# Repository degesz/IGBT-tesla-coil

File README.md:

# IGBT-tesla-coil
tesla coil design with IGBT swithced H bridge

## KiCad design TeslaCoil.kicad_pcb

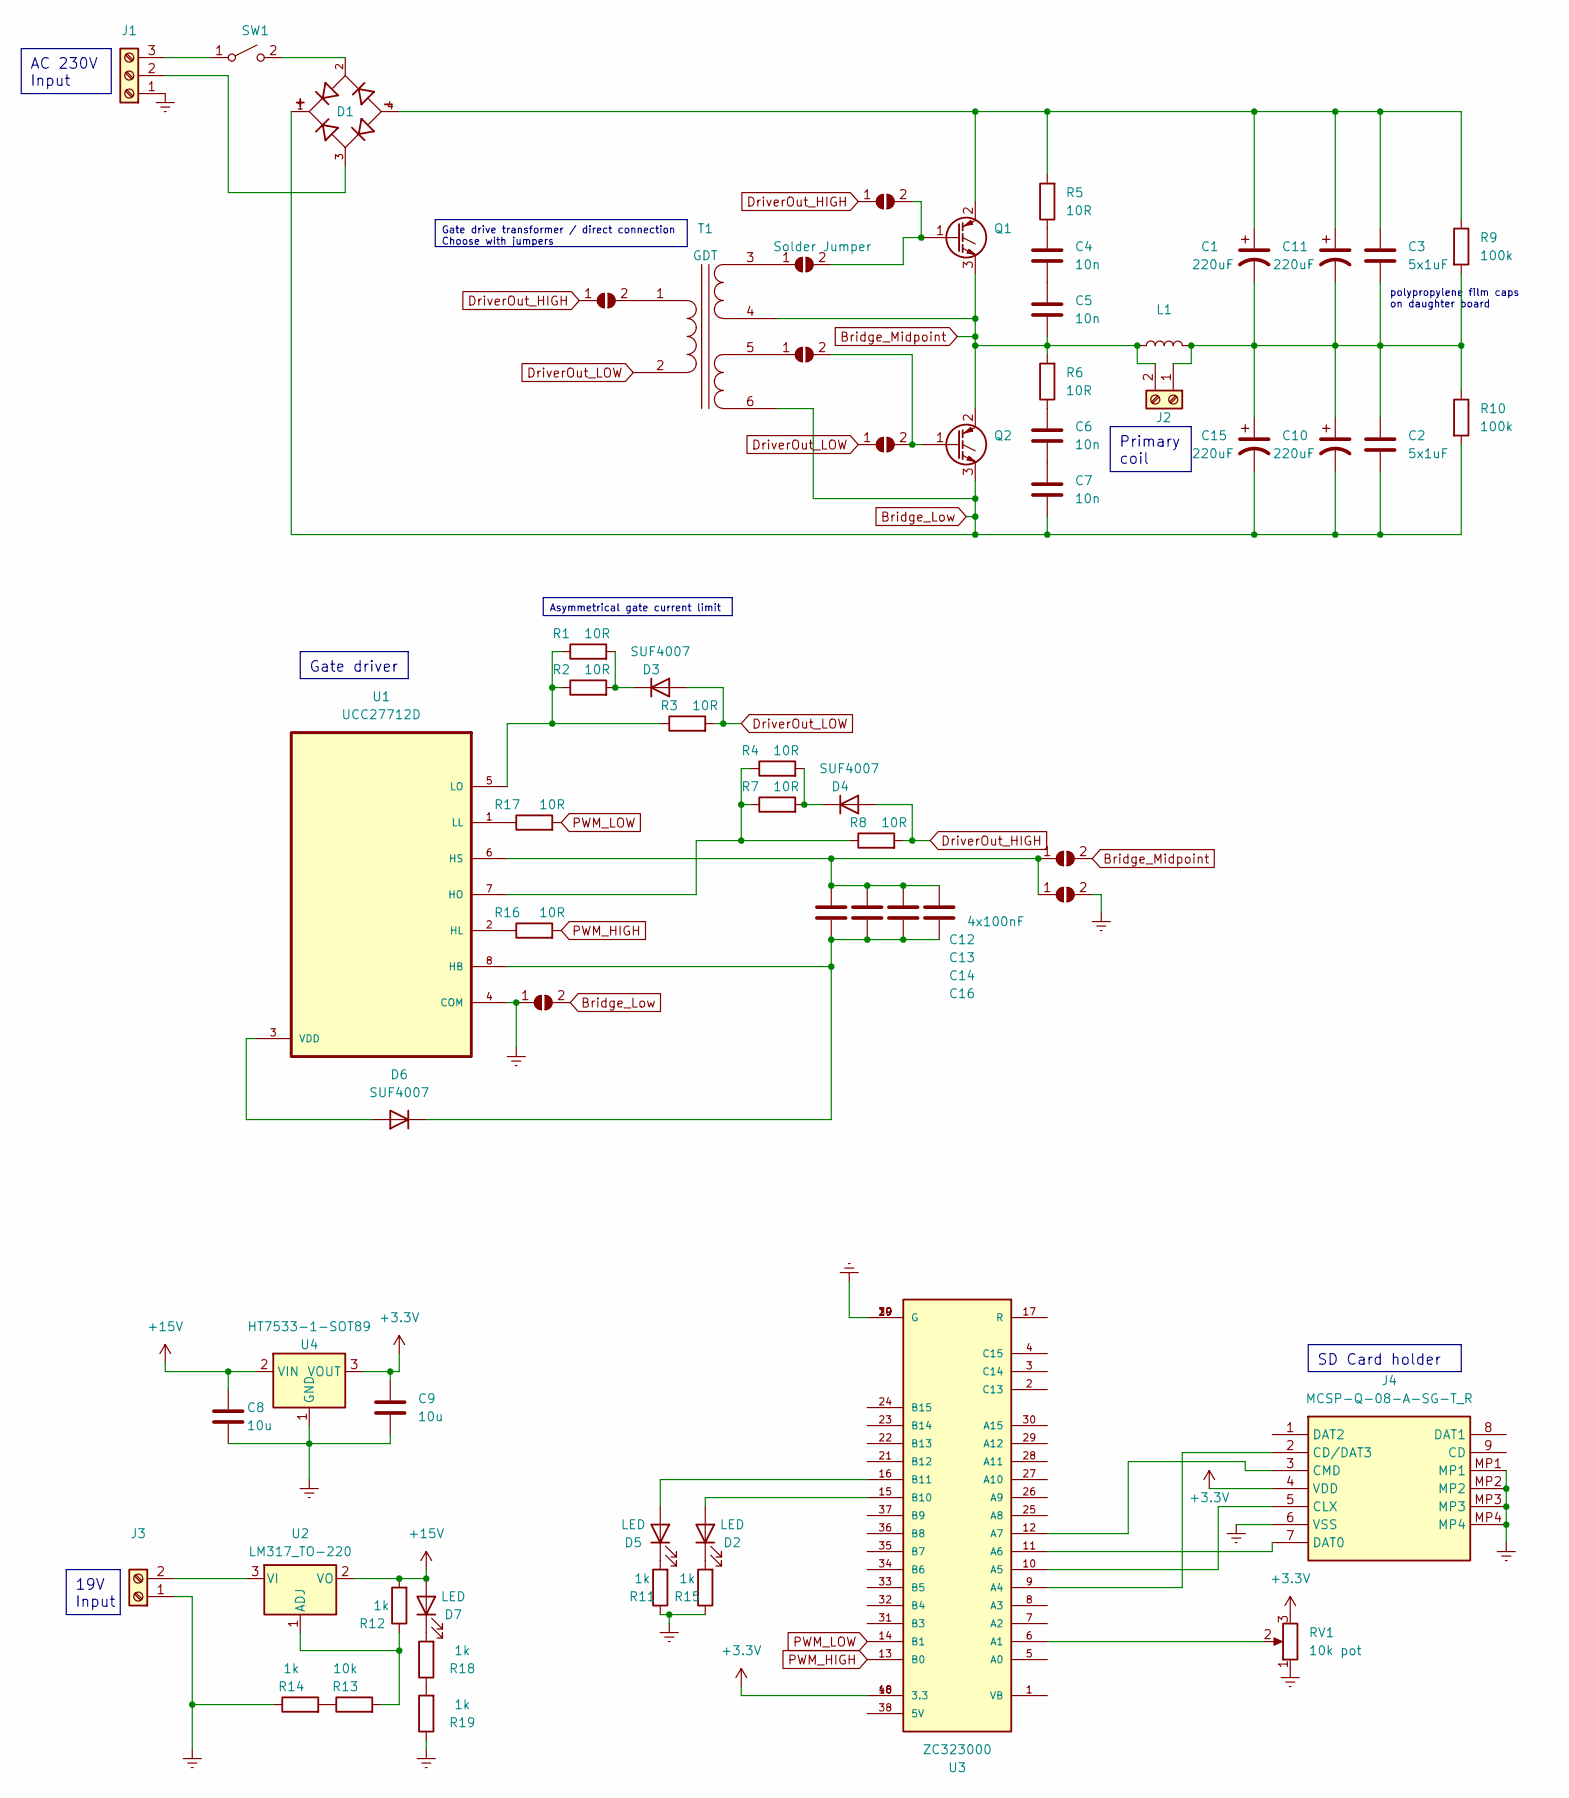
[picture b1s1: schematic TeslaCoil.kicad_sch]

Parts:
C1, C10, C11, C15: 220uF; CP_Radial_D22.0mm_P10.00mm_SnapIn
C2, C3: 5x1uF; C_Rect_L18.0mm_W5.0mm_P15.00mm_FKS3_FKP3
C4, C5, C6, C7: 10n; C_Rect_L13.0mm_W5.0mm_P10.00mm_FKS3_FKP3_MKS4
C8, C9: 10u; C_0805_2012Metric_Pad1.18x1.45mm_HandSolder
C12, C13, C14: 100nF; C_0603_1608Metric
C16: 4x100nF; C_0603_1608Metric
D1: GBJ1008-BP; GBJ1008-BP_DIOB_GBJ1008-BP
D2, D5, D7: LED; LED_0805_2012Metric
D3, D4, D6: SUF4007; D_MELF_Handsoldering
J1: Screw_Terminal_01x03; TerminalBlock_4Ucon_1x03_P3.50mm_Horizontal
J2, J3: Screw_Terminal_01x02; TerminalBlock_4Ucon_1x02_P3.50mm_Horizontal
J4: MCSP-Q-08-A-SG-T_R; MCSPQ08ASGTR; Manufacturer_Part_Number MCSP-Q-08-A-SG-T/R
JP1, JP2, JP3, JP4, JP5, JP6, JP7, JP8: Solder Jumper; SolderJumper-2_P1.3mm_Open_TrianglePad1.0x1.5mm
L1: L
Q1, Q2: Q_NIGBT_GCE; TO-247-3_Vertical
R1, R2, R3, R4, R7, R8, R16, R17: 10R; R_0603_1608Metric_Pad0.98x0.95mm_HandSolder
R5, R6: 10R; R_Axial_Power_L25.0mm_W9.0mm_P10.16mm_Vertical
R9, R10: 100k; R_Axial_DIN0207_L6.3mm_D2.5mm_P7.62mm_Horizontal
R11, R12, R14, R15, R18, R19: 1k; R_0603_1608Metric_Pad0.98x0.95mm_HandSolder
R13: 10k; R_0603_1608Metric_Pad0.98x0.95mm_HandSolder
RV1: 10k pot; potentiometer
SW1: SW_SPST; Rocker switch
T1: GDT; Transformer_Toroid_Tapped_Horizontal_D10.5mm_Amidon-T37
U1: UCC27712D; UCC27712D_SOIC127P599X175-8N
U2: LM317_TO-220; TO-220-3_Vertical
U3: ZC323000; ZC323000_MODULE_ZC323000; PARTREV N/A
U4: HT7533-1-SOT89; SOT-89-3

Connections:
+3.3V: C9.1, J4.4 (VDD), RV1.3, U3.18 (3.3), U3.40 (3.3), U4.3 (VOUT)
+15V: C8.1, D7.2 (A), R12.2, U2.2 (VO), U4.2 (VIN)
Bridge_Low: C2.2, C7.2, C10.2, C15.2, D1.1, JP8.2 (B), Q2.3 (E), R10.2, T1.6 (SD)
Bridge_Midpoint: C5.2, J2.2, JP6.2 (B), L1.1, Q1.3 (E), Q2.2 (C), R6.2, T1.4 (SB)
DriverOut_HIGH: D4.2 (A), JP3.1 (A), JP5.1 (A), R8.2
DriverOut_LOW: D3.2 (A), JP4.1 (A), R3.2, T1.2 (AB)
Earth: C8.2, C9.2, J1.1, J3.1, J4.6 (VSS), J4.MP1, J4.MP2, J4.MP3, J4.MP4, JP7.2 (B), JP8.1 (A), R11.1, R14.1, R15.1, R19.1, RV1.1, U1.4 (COM), U3.19 (G), U3.20 (G), U3.39 (G), U4.1 (GND)
unnamed: C4.1, R5.1
unnamed: C4.2, C5.1
unnamed: C6.1, R6.1
unnamed: C6.2, C7.1
unnamed: D2.2 (A), U3.15 (B10)
unnamed: D2.1 (K), R15.2
unnamed: D3.1 (K), R1.2, R2.2
unnamed: D4.1 (K), R4.2, R7.2
unnamed: D5.2 (A), U3.16 (B11)
unnamed: D5.1 (K), R11.2
unnamed: D6.2 (A), U1.3 (VDD)
unnamed: C12.2, C13.2, C14.2, C16.2, D6.1 (K), U1.8 (HB)
unnamed: D7.1 (K), R18.2
unnamed: D1.3, J1.2
unnamed: J1.3, SW1.1 (A)
unnamed: C1.2, C2.1, C3.2, C10.1, C11.2, C15.1, J2.1, L1.2, R9.2, R10.1
unnamed: J3.2, U2.3 (VI)
unnamed: J4.2 (CD/DAT3), U3.9 (A4)
unnamed: J4.5 (CLX), U3.10 (A5)
unnamed: J4.3 (CMD), U3.12 (A7)
unnamed: J4.7 (DAT0), U3.11 (A6)
unnamed: JP1.1 (A), T1.3 (SA)
unnamed: JP1.2 (B), JP5.2 (B), Q1.1 (G)
unnamed: JP2.1 (A), T1.5 (SC)
unnamed: JP2.2 (B), JP4.2 (B), Q2.1 (G)
unnamed: JP3.2 (B), T1.1 (AA)
unnamed: C12.1, C13.1, C14.1, C16.1, JP6.1 (A), JP7.1 (A), U1.6 (HS)
unnamed: C1.1, C3.1, C11.1, D1.4, Q1.2 (C), R5.2, R9.1
unnamed: R13.1, R14.2
unnamed: R18.1, R19.2
unnamed: D1.2, SW1.2 (B)
unnamed: R16.1, U1.2 (HL)
unnamed: R4.1, R7.1, R8.1, U1.7 (HO)
unnamed: R17.1, U1.1 (LL)
unnamed: R1.1, R2.1, R3.1, U1.5 (LO)
unnamed: R12.1, R13.2, U2.1 (ADJ)
unnamed: RV1.2, U3.6 (A1)
PWM_HIGH: R16.2, U3.13 (B0)
PWM_LOW: R17.2, U3.14 (B1)

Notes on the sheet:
SD Card holder
Primary coil
Gate drive transformer / direct connection Choose with jumpers
19V Input
AC 230V Input
Asymmetrical gate current limit
Gate driver
polypropylene film caps on daughter board

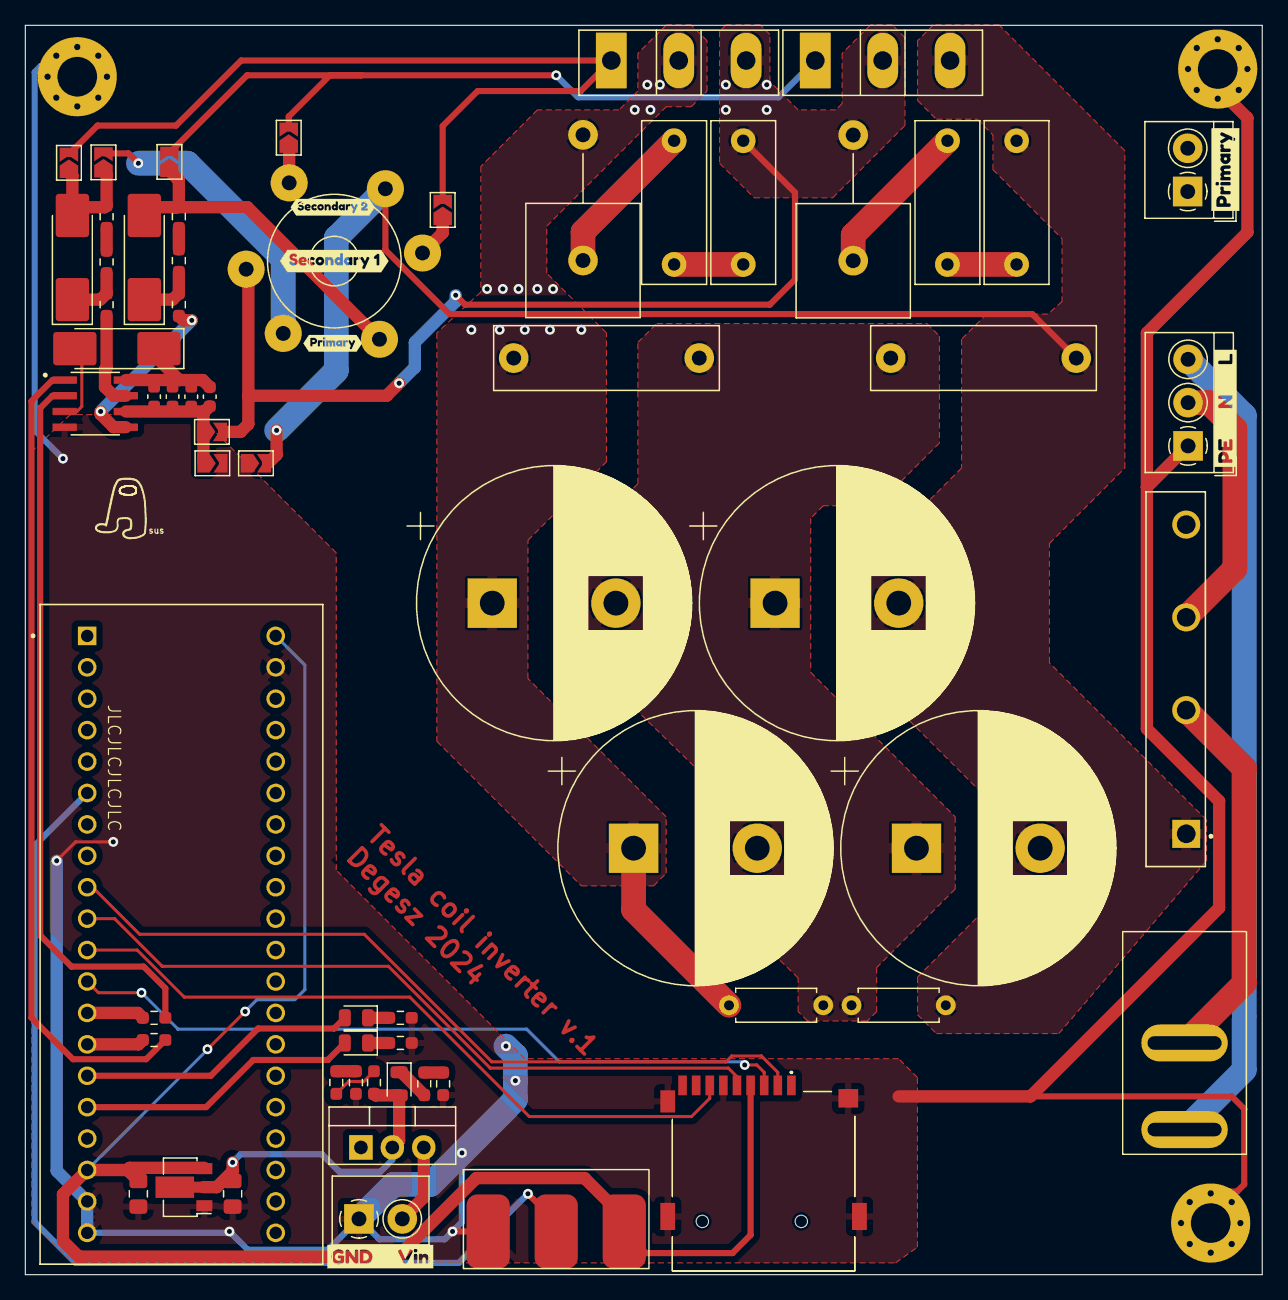
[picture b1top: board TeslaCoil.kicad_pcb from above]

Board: 2 copper layers, 100.0 x 101.0 mm, 69 parts (0 on the bottom side), 46 nets.

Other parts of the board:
kibuzzard-65B38B8A: G***; kibuzzard-65B38B8A
kibuzzard-65B38BA7: G***; kibuzzard-65B38BA7
kibuzzard-65B38BC8: G***; kibuzzard-65B38BC8
kibuzzard-65B138E2: G***; kibuzzard-65B138E2
kibuzzard-65B13903: G***; kibuzzard-65B13903
kibuzzard-65B13918: G***; kibuzzard-65B13918

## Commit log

2024-01-21 remove prod folder form git
2024-01-21 half bridge schematic
2024-01-21 add gate driver
2024-01-21 footprints
2024-01-22 layout mockup
2024-01-25 layout 2nd rev
2024-01-25 routing, power traces
2024-01-25 amogus
2024-01-26 final v1
2024-01-26 production v1
